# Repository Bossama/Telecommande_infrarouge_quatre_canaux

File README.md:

# Telecommande_infrarouge_quatre_canaux

Notre Mini Projet intituler télécommande a 4 cannas composer de deux cartes électroniques :

Le 1er est un émetteur possède 4 bouton dont chaque à leur propre période 

Le 2 -ème est un récepteur qui va traiter le signal délivrer par l’émetteur et puis (après une phase de sélection) ce signal va 
assurer soit la mise en marche ou l’arrêt de l’une des 4 canaux dont deux voix en 12V DC et deux autres en 220V AC. 

Programme utiliser : Eagle 7.7 win64
                     https://www.autodesk.com/products/eagle/overview

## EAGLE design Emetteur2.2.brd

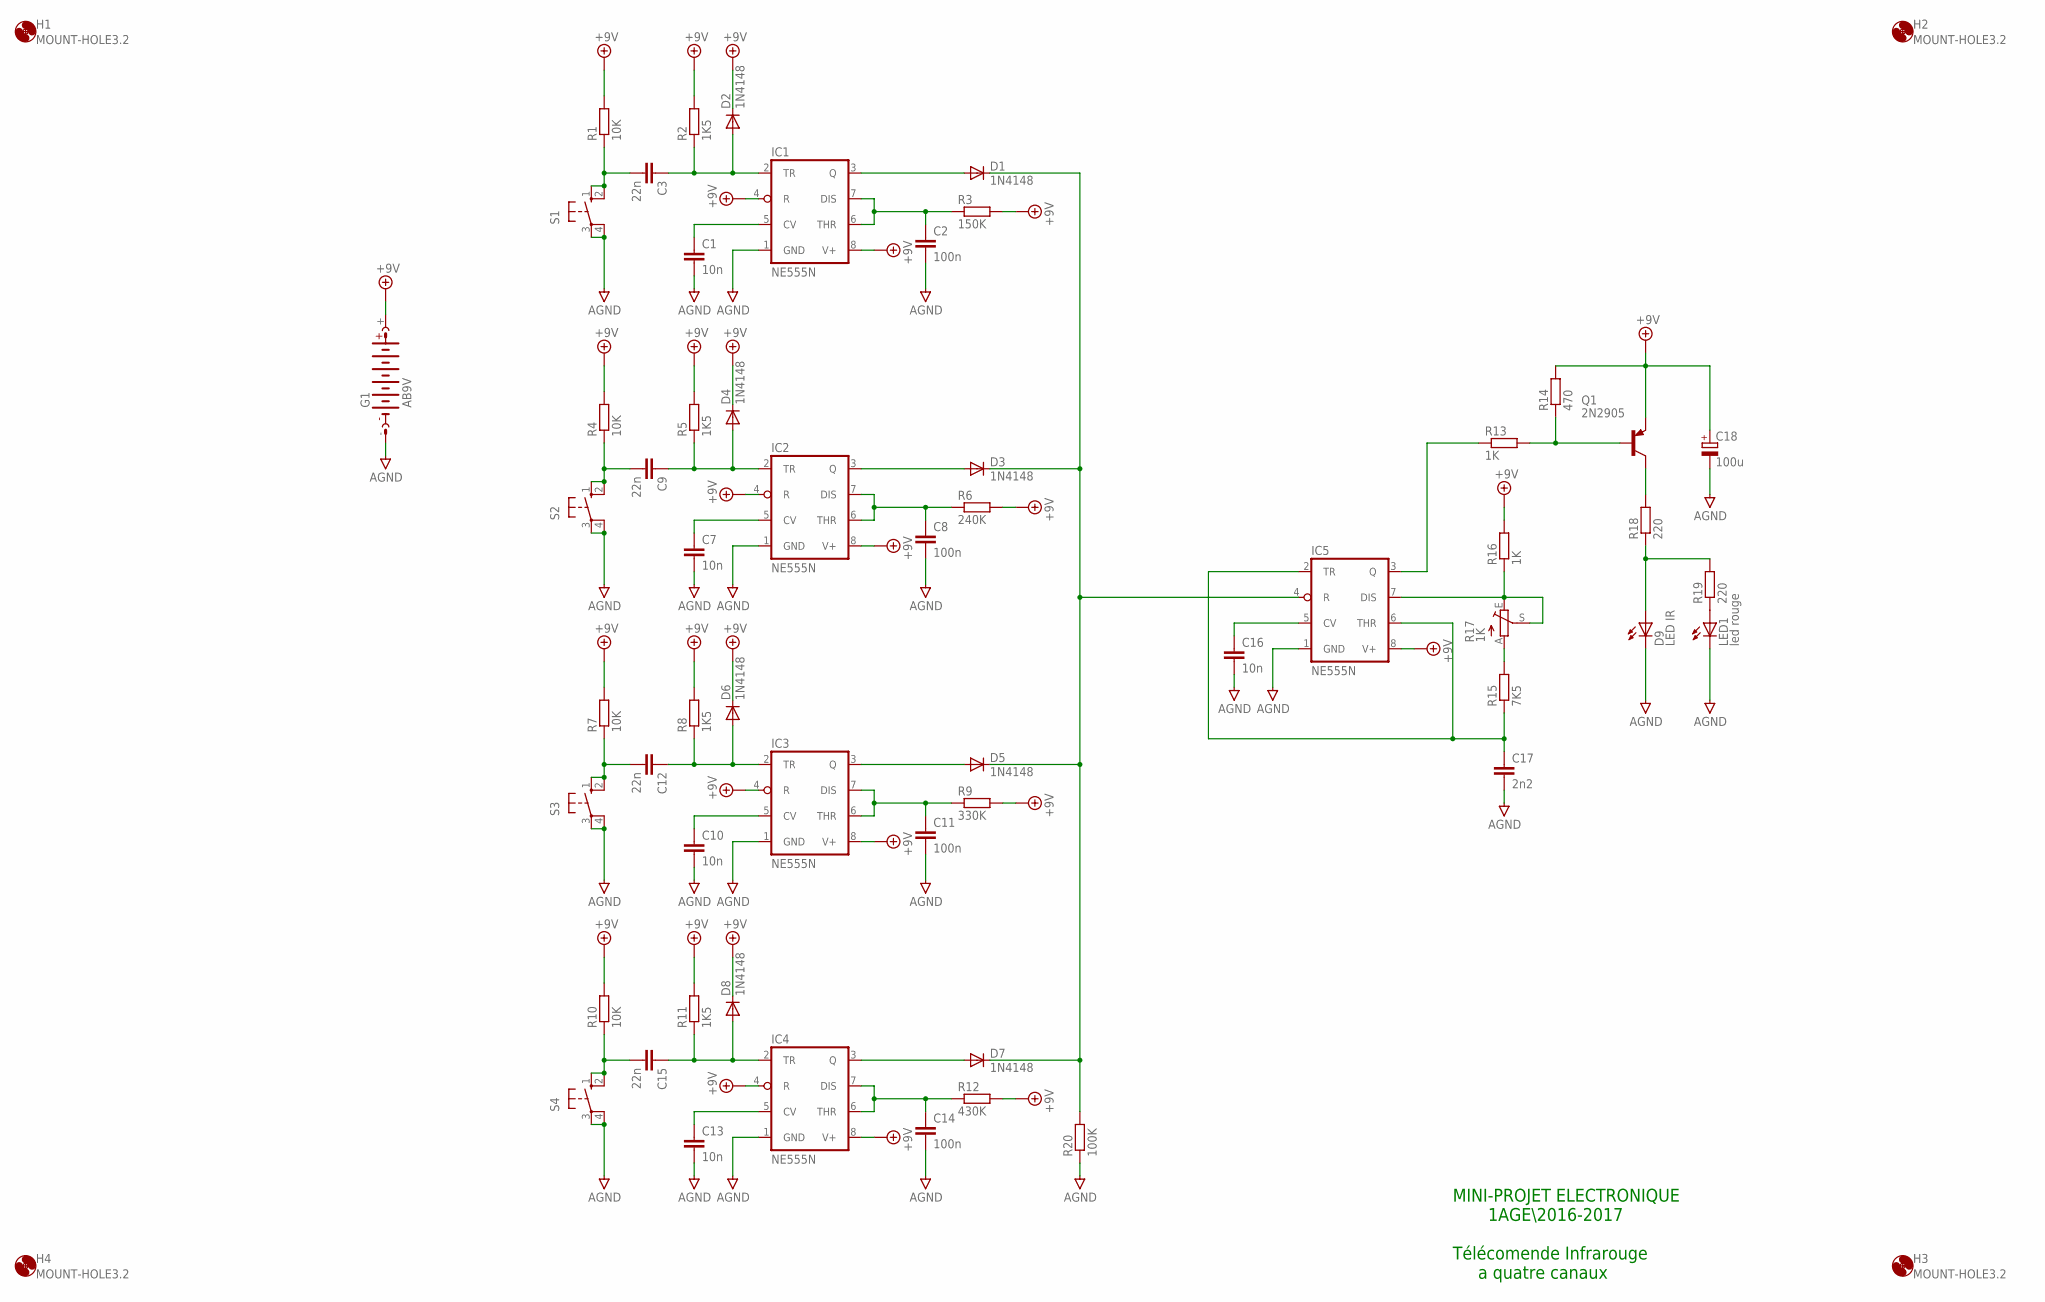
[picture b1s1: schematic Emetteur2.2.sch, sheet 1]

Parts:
C1, C7, C10, C13, C16: 10n; C050-025X075
C2, C8, C11, C14: 100n; C050-030X075
C3, C9, C12, C15: 22n; C050-025X075
C17: 2n2; C050-025X075
C18: 100u; E5-4
D1, D2, D3, D4, D5, D6, D7, D8: 1N4148; DO35-7
D9: LED IR; SFH482
G1: AB9V
H1, H2, H3, H4: MOUNT-HOLE3.2; 3,2
IC1, IC2, IC3, IC4, IC5: NE555N; DIL08
LED1: led rouge; LED3MM
Q1: 2N2905; TO5
R1, R4, R7, R10: 10K; 0207/12
R2, R5, R8, R11: 1K5; 0207/10
R3: 150K; 0204/7
R6: 240K; 0204/7
R9: 330K; 0204/7
R12: 430K; 0204/7
R13, R16: 1K; 0207/12
R14: 470; 0207/10
R15: 7K5; 0207/10
R17: 1K; B25P
R18, R19: 220; 0207/10
R20: 100K; 0207/10
S1: B3F-10XX
S2, S3, S4: 10-XX; B3F-10XX

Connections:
+9V: C18.+, D2.C, D4.C, D6.C, D8.C, G1.+, IC1.4 (R), IC1.8 (V+), IC2.4 (R), IC2.8 (V+), IC3.4 (R), IC3.8 (V+), IC4.4 (R), IC4.8 (V+), IC5.8 (V+), Q1.1 (E), R1.2, R2.2, R3.2, R4.2, R5.2, R6.2, R7.2, R8.2, R9.2, R10.2, R11.2, R12.2, R14.2, R16.2
AGND: C1.2, C2.2, C7.2, C8.2, C10.2, C11.2, C13.2, C14.2, C16.2, C17.2, C18.-, D9.K (C), G1.-, IC1.1 (GND), IC2.1 (GND), IC3.1 (GND), IC4.1 (GND), IC5.1 (GND), LED1.K (C), R20.1, S1.3, S1.4 (P1), S2.3, S2.4 (P1), S3.3, S3.4 (P1), S4.3, S4.4 (P1)
unnamed: C1.1, IC1.5 (CV)
unnamed: C3.1, D2.A, IC1.2 (TR), R2.1
unnamed: C2.1, IC1.6 (THR), IC1.7 (DIS), R3.1
unnamed: C3.2, R1.1, S1.1 (S), S1.2 (S1)
unnamed: D1.A, IC1.3 (Q)
unnamed: IC5.3 (Q), R13.1
unnamed: C7.1, IC2.5 (CV)
unnamed: C9.1, D4.A, IC2.2 (TR), R5.1
unnamed: C8.1, IC2.6 (THR), IC2.7 (DIS), R6.1
unnamed: C9.2, R4.1, S2.1 (S), S2.2 (S1)
unnamed: D3.A, IC2.3 (Q)
unnamed: D1.C, D3.C, D5.C, D7.C, IC5.4 (R), R20.2
unnamed: C10.1, IC3.5 (CV)
unnamed: C12.1, D6.A, IC3.2 (TR), R8.1
unnamed: C11.1, IC3.6 (THR), IC3.7 (DIS), R9.1
unnamed: C12.2, R7.1, S3.1 (S), S3.2 (S1)
unnamed: D5.A, IC3.3 (Q)
unnamed: Q1.3 (C), R18.2
unnamed: C13.1, IC4.5 (CV)
unnamed: C15.1, D8.A, IC4.2 (TR), R11.1
unnamed: C14.1, IC4.6 (THR), IC4.7 (DIS), R12.1
unnamed: C15.2, R10.1, S4.1 (S), S4.2 (S1)
unnamed: D7.A, IC4.3 (Q)
unnamed: R15.2, R17.A
unnamed: C16.1, IC5.5 (CV)
unnamed: C17.1, IC5.2 (TR), IC5.6 (THR), R15.1
unnamed: IC5.7 (DIS), R16.1, R17.E, R17.S
unnamed: Q1.2 (B), R13.2, R14.1
unnamed: D9.A, R18.1, R19.2
unnamed: LED1.A, R19.1

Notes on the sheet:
MINI-PROJET ELECTRONIQUE 1AGE\2016-2017 Télécomende Infrarouge a quatre canaux

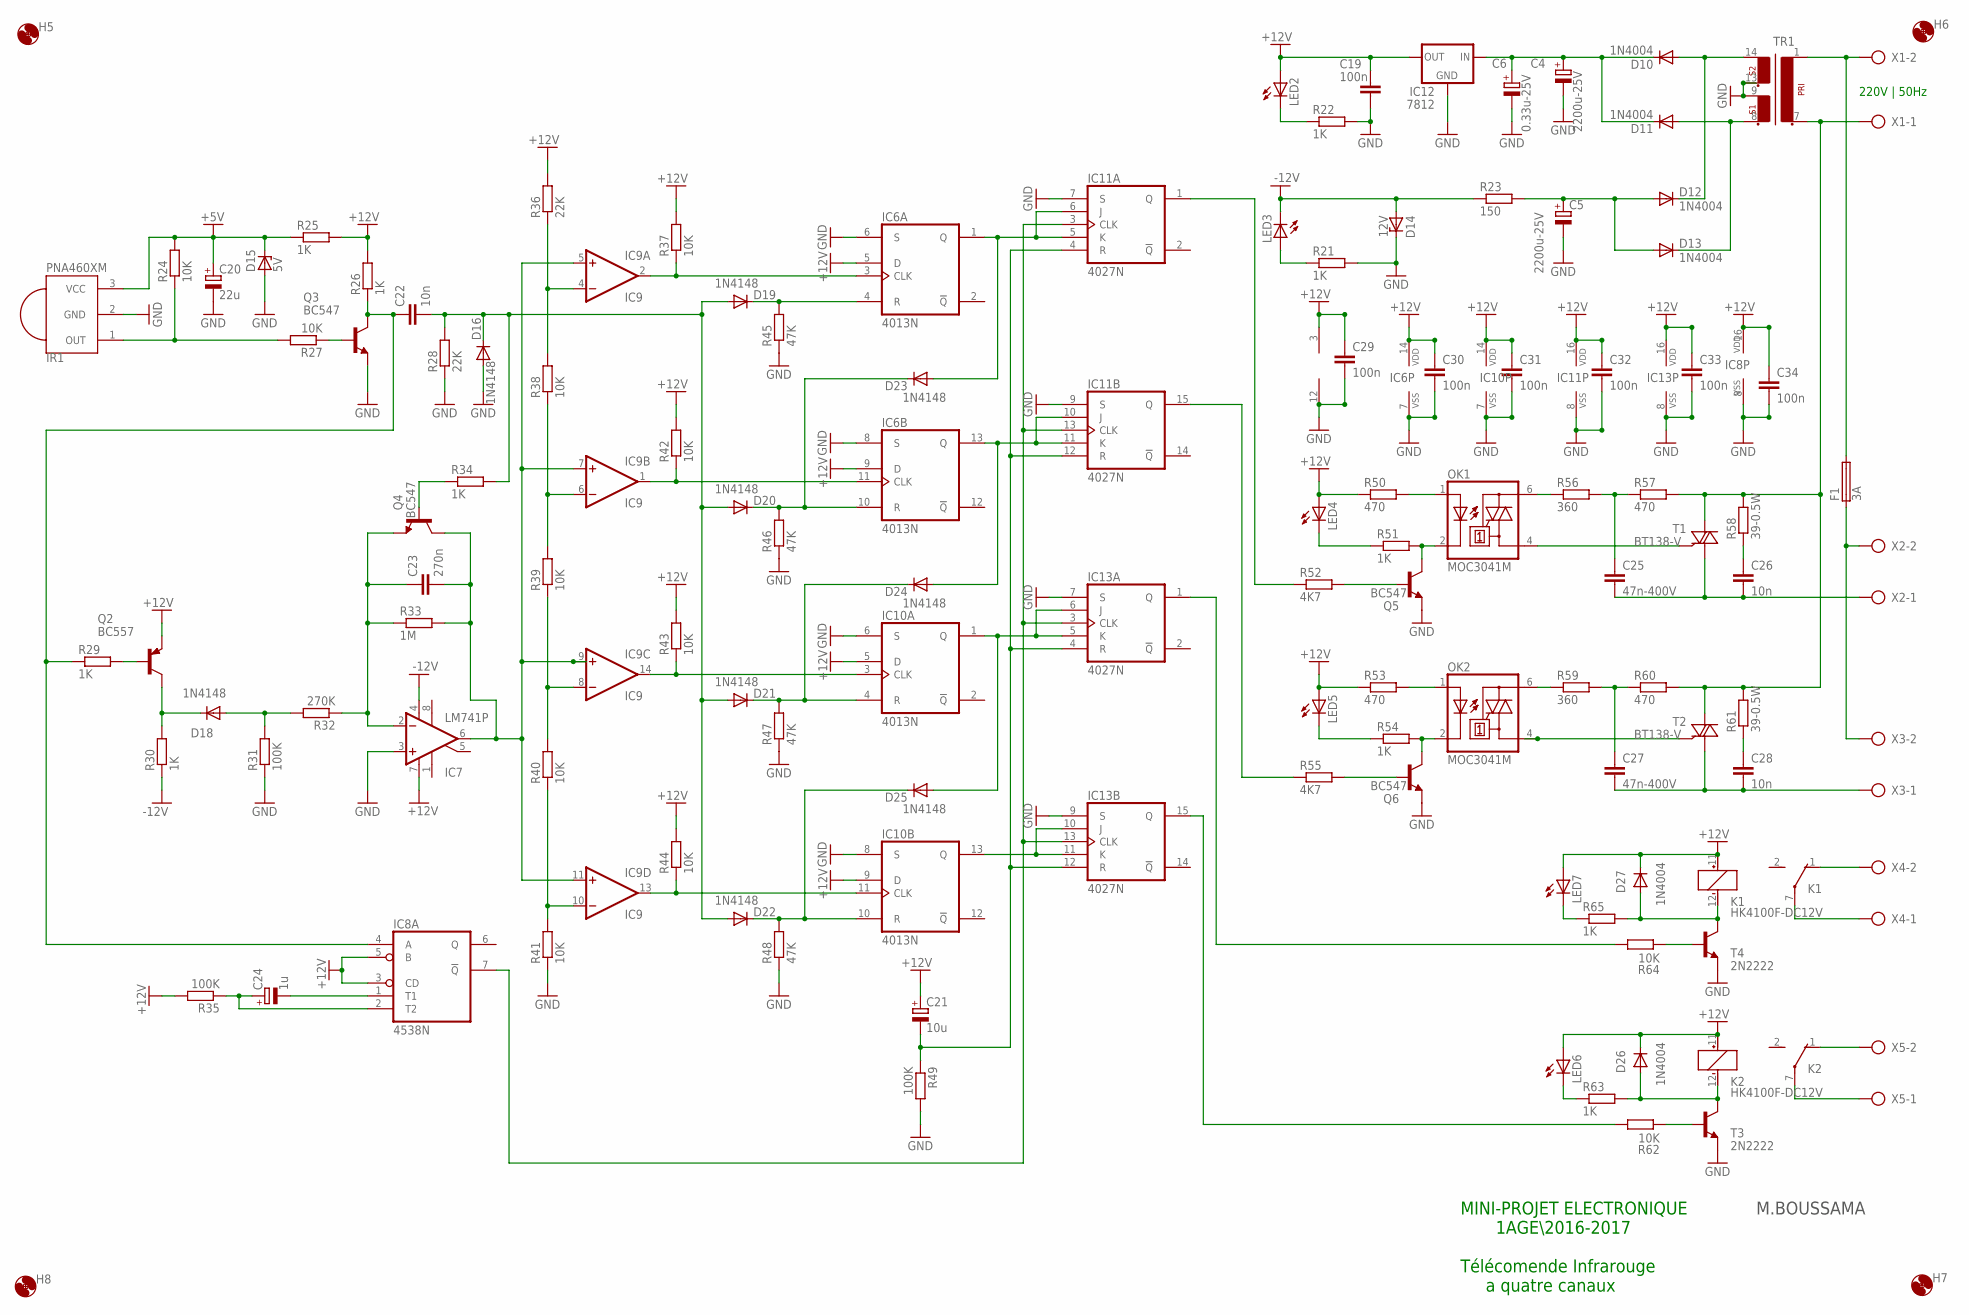
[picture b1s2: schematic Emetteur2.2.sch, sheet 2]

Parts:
C4, C5: 2200u-25V; E5-13
C6: 0.33u-25V; E5-5
C19, C29, C30, C31, C32, C33, C34: 100n; C050-025X075
C20: 22u; E2,5-6
C21: 10u; E2,5-6E
C22: 10n; C050-025X075
C23: 270n; C050-035X075
C24: 1u; E2,5-6E
C25, C27: 47n-400V; C150-054X183
C26, C28: 10n; C102-043X133
D10, D11, D12, D13, D26, D27: 1N4004; DO41-10
D14: 12V; DO41Z10
D15: 5V; DO41Z10
D16, D19, D21, D23, D25: 1N4148; DO35-10
D18: 1N4148; DO35-7
D20, D22, D24: 1N4148; SOD61B
F1: 3A; GSH15
H5, H6, H7, H8: MOUNT-HOLE3.2; 3,2
IC6, IC10: 4013N; DIL14
IC7: LM741P; DIL08
IC8: 4538N; DIL16
IC9: IC9; DIL14
IC11, IC13: 4027N; DIL16
IC12: 7812; 78XXS
IR1: PNA460XM
K1, K2: HK4100F-DC12V; SMR1
LED2, LED3, LED4, LED5, LED6, LED7: LED3MM
OK1, OK2: MOC3041M; DIL06
Q2: BC557; TO92-EBC
Q3, Q4, Q5, Q6: BC547; TO92-EBC
R21, R22, R25, R30, R51, R54, R63, R65: 1K; 0207/10
R23: 150; 0207/10
R24, R27, R37, R38, R39, R40, R41, R42, R43, R44: 10K; 0207/10
R26, R34: 1K; 0207/12
R28, R36: 22K; 0207/10
R29: 1K; 0207/15
R31, R35: 100K; 0207/10
R32: 270K; 0207/12
R33: 1M; 0207/10
R45, R46, R47: 47K; 0207/12
R48: 47K; 0207/10
R49: 100K; 0207/12
R50, R53, R57, R60: 470; 0207/10
R52, R55: 4K7; 0207/10
R56, R59: 360; 0207/10
R58, R61: 39-0.5W; 0207/10
R62, R64: 10K; 0207/12
T1, T2: BT138-V; TO220BV
T3, T4: 2N2222; TO92-EBC-OVAL
TR1: EI54-2
X1, X2, X3, X4, X5: AK300/2

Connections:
+5V: C20.+, D15.C, IR1.3 (VCC), R24.2, R25.1
+12V: C19.1, C21.+, C29.1, C30.1, C31.1, C32.1, C33.1, C34.1, D26.C, D27.C, IC6.5 (D), IC6.9 (D), IC6.14 (VDD), IC7.7 (V+), IC8.3 (CD), IC8.5 (B), IC8.16 (VDD), IC9.3 (V+), IC10.5 (D), IC10.9 (D), IC10.14 (VDD), IC11.16 (VDD), IC12.OUT, IC13.16 (VDD), K1.11 (+), K2.11 (+), LED2.A, LED4.A, LED5.A, LED6.A, LED7.A, Q2.E, R25.2, R26.2, R35.2, R36.2, R37.2, R42.2, R43.2, R44.2, R50.1, R53.1
-12V: D14.A, IC7.4 (V-), LED3.K (C), R23.1, R30.1
GND: C4.-, C5.-, C6.-, C19.2, C20.-, C29.2, C30.2, C31.2, C32.2, C33.2, C34.2, D14.C, D15.A, D16.A, IC6.6 (S), IC6.7 (VSS), IC6.8 (S), IC7.3 (+IN), IC8.8 (VSS), IC9.12 (GND), IC10.6 (S), IC10.7 (VSS), IC10.8 (S), IC11.7 (S), IC11.8 (VSS), IC11.9 (S), IC12.GND, IC13.7 (S), IC13.8 (VSS), IC13.9 (S), IR1.2 (GND), Q3.E, Q5.E, Q6.E, R21.2, R22.2, R28.1, R31.1, R41.1, R45.1, R46.1, R47.1, R48.1, R49.2, T3.E, T4.E, TR1.9 (4), TR1.13 (5)
unnamed: F1.2, TR1.1, X1.2
unnamed: R57.2, R58.2, R60.2, R61.2, T1.T2 (A2), T2.T2 (A2), TR1.7 (2), X1.1
unnamed: Q3.B, R27.1
unnamed: D10.A, D12.C, TR1.14 (6)
unnamed: D11.A, D13.C, TR1.8 (3)
unnamed: C4.+, C6.+, D10.C, D11.C, IC12.IN
unnamed: C5.+, D12.A, D13.A, R23.2
unnamed: LED3.A, R21.1
unnamed: IR1.1 (OUT), R24.1, R27.2
unnamed: IC6.3 (CLK), IC9.2 (OUT), R37.1
unnamed: LED2.K (C), R22.1
unnamed: Q2.B, R29.2
unnamed: D18.C, Q2.C, R30.2
unnamed: D18.A, R31.2, R32.2
unnamed: C23.1, IC7.2 (-IN), Q4.E, R32.1, R33.1
unnamed: D20.C, D23.C, IC6.10 (R), R46.2
unnamed: C22.1, IC8.4 (A), Q3.C, R26.1, R29.1
unnamed: C23.2, IC7.6 (OUT), IC9.5 (+IN), IC9.7 (+IN), IC9.9 (+IN), IC9.11 (+IN), Q4.C, R33.2
unnamed: Q4.B, R34.1
unnamed: C24.+, IC8.2 (T2), R35.1
unnamed: C24.-, IC8.1 (T1)
unnamed: IC9.4 (-IN), R36.1, R38.2
unnamed: IC9.10 (-IN), R40.1, R41.2
unnamed: IC9.8 (-IN), R39.1, R40.2
unnamed: IC9.6 (-IN), R38.1, R39.2
unnamed: IC6.11 (CLK), IC9.1 (OUT), R42.1
unnamed: IC9.14 (OUT), IC10.3 (CLK), R43.1
unnamed: IC9.13 (OUT), IC10.11 (CLK), R44.1
unnamed: D23.A, IC6.1 (Q), IC11.5 (K), IC11.6 (J)
unnamed: D24.A, IC6.13 (Q), IC11.10 (J), IC11.11 (K)
unnamed: Q5.B, R52.2
unnamed: IC10.13 (Q), IC13.10 (J), IC13.11 (K)
unnamed: C21.-, IC11.4 (R), IC11.12 (R), IC13.4 (R), IC13.12 (R), R49.1
unnamed: D25.A, IC10.1 (Q), IC13.5 (K), IC13.6 (J)
unnamed: IC11.1 (Q), R52.1
unnamed: LED4.K (C), R51.1
unnamed: OK1.2 (C), Q5.C, R51.2
unnamed: Q6.B, R55.2
unnamed: IC11.15 (Q), R55.1
unnamed: LED5.K (C), R54.1
unnamed: OK2.2 (C), Q6.C, R54.2
unnamed: OK1.1 (A), R50.2
unnamed: OK2.1 (A), R53.2
unnamed: F1.1, X2.2, X3.2
unnamed: C27.1, R59.2, R60.1
unnamed: C25.1, R56.2, R57.1
unnamed: C25.2, C26.2, T1.T1 (A1), X2.1
unnamed: C26.1, R58.1
unnamed: C27.2, C28.2, T2.T1 (A1), X3.1
unnamed: OK1.4 (A1), T1.G
unnamed: D26.A, K2.12 (-), R63.2, T3.C
unnamed: C28.1, R61.1
unnamed: OK2.4 (A1), T2.G
unnamed: OK1.6 (A2), R56.1
unnamed: OK2.6 (A2), R59.1
unnamed: R62.1, T3.B
unnamed: K2.1 (O), X5.2
unnamed: K2.7, X5.1
unnamed: LED6.K (C), R63.1
unnamed: D27.A, K1.12 (-), R65.2, T4.C
unnamed: R64.1, T4.B
unnamed: K1.7, X4.1
unnamed: K1.1 (O), X4.2
unnamed: LED7.K (C), R65.1
unnamed: IC13.1 (Q), R64.2
unnamed: IC13.15 (Q), R62.2
unnamed: IC8.7 (!Q), IC11.3 (CLK), IC11.13 (CLK), IC13.3 (CLK), IC13.13 (CLK)
unnamed: D22.C, D25.C, IC10.10 (R), R48.2
unnamed: D19.C, IC6.4 (R), R45.2
unnamed: C22.2, D16.C, D19.A, D20.A, D21.A, D22.A, R28.2, R34.2
unnamed: D21.C, D24.C, IC10.4 (R), R47.2

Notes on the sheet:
220V | 50Hz
MINI-PROJET ELECTRONIQUE 1AGE\2016-2017 Télécomende Infrarouge a quatre canaux
M.BOUSSAMA

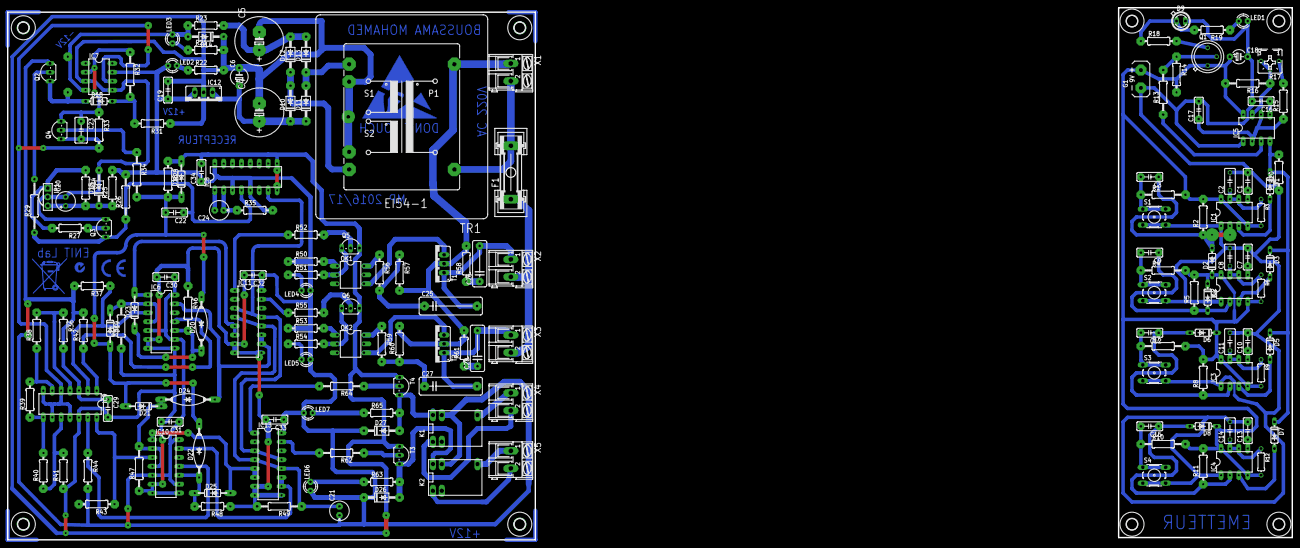
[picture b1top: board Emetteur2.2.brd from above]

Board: 2 copper layers, 366.4 x 151.8 mm, 184 parts (1 on the bottom side), 107 nets.

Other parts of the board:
U$1: DON'T TOUCH; ESD
U$3: MUELLTONNE_10.00
U$11: CE_5MM
U$12: C_TICK-3MM

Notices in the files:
parts and their libraries:
supply0: Copyright (C) 2007, Bob Starr
